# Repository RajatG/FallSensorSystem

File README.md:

# Fall Sensor System (IoT Firmware, KiCad PCB Hardware & Android Mobile App)

An ultra-low-power, dual-radar fall detection and room occupancy monitoring system engineered for ceiling and wall mounting with battery autonomy.

---

## 📁 Repository Overview

```
├── firmware/                        # Microcontroller & Radar Firmware
│   ├── fall_sensor_esp32_C1001_v1/  # ESP32 Firmware for C1001 60GHz Radar (v4.23)
│   ├── fall_sensor_esp32_ld2410_v1/ # ESP32 Firmware for LD2410 24GHz Radar (v4.23)
│   ├── fall_attiny_v1/              # ATtiny85 Low-Power Wake Sentinel (v4.8)
│   └── fall_attiny_mic_debug/       # ATtiny85 MIC Hardware Debug Utility
│
├── hardware/                        # KiCad 10.0 PCB & Schematic Files
│   ├── fall_sensor.kicad_sch        # Main System Schematic
│   ├── fall_sensor.kicad_pcb        # 2-Layer PCB Layout
│   ├── fall_sensor.kicad_pro        # KiCad Project Configuration
│   ├── FallSensor.kicad_sym     # Custom Symbol Library
│   ├── FallSensor.pretty/       # Custom Footprint Library
│   └── export/
│       ├── fall_sensor_gerbers.zip  # Production Gerber & Drill Package (JLCPCB/PCBWay)
│       └── pdf/                     # Printable Documentation (See hardware/export/pdf/README.md)
│           ├── fall_sensor_pcb_front_and_back_A4.pdf  # 1:1 True Scale Paper Testing Sheet
│           ├── fall_sensor_schematic_A4_printable.pdf # Printable A4 Schematic
│           ├── assembly/            # Top & Bottom Assembly Drawings
│           ├── layers/              # Top & Bottom Copper Layer Plots
│           └── schematic/           # Full-Size A3 Engineering Schematic
│
├── enclosure/                       # 3D Printed Wall-Mount Enclosure (v2.1 Square)
│   ├── fall_sensor_enclosure_base.stl # Base Mount with 18650 Battery Bay & PCB Standoffs
│   ├── fall_sensor_enclosure_lid.stl  # Front Cover with Apertures & Alignment Lip
│   ├── build_square_enclosure.py      # Parametric Blender Python CAD Script (v2.1)
│   ├── fall_sensor_enclosure.blend    # Master Blender CAD Project & Studio Renders
│   └── README.md                      # Mechanical Specifications & Slicer Guide
│
├── mobile_app/                      # Android Companion App (Jetpack Compose)
│   ├── app/                         # Source Code supporting C1001 & LD2410 Flavors
│   ├── build.gradle.kts
│   └── ...
│
└── docs/                            # Architectural Specs, Roadmaps & Engineering Docs (See docs/README.md)
    ├── README.md                    # Master Documentation Hub & Flow Map
    ├── Firmware_Architecture_and_Detection_Logic.md  # Complete Firmware Logic & 4-Layer Fall Pipeline
    ├── Master_4Stream_Roadmap_and_Recommendations.md # Comprehensive 4-Stream Status & Production Roadmap
    ├── PCB_Component_Connections_Verification.md     # Master 21-Component Netlist & Pinout Verification Guide
    ├── PCB_Component_Footprints_and_Dimensions.md    # Physical Dimensions, Drills & Pad Pitch Reference
    ├── SMD_BOM_Master_List.md       # Production SMD Component Master List (Rev B)
    ├── SMD_Hardware_Architecture.md # Power-path, Charger & Protection Circuitry Specs
    ├── C1001_Early_Exit_Analysis.md # Radar Optimization & Timing Breakdown
    └── ATtiny85_MIC_Analysis.md     # Sentinel Threshold & Acoustic Filter Specs
```

---

## ⚡ System Overview & Architecture

### What the System Is
The **Fall Sensor System** is a privacy-first, contactless room occupancy and fall detection device designed for elder care and clinical environments. It eliminates the need for cameras, audio-recording microphones, or wearable pendants.

### How it Works: The Staged-Wakeup Architecture
Operating mmWave radar continuously requires 60–120 mA, which would exhaust a battery in under two days. To achieve long battery life on a single 18650 cell, the system uses an **asymmetric staged-wakeup architecture**:

```
+-----------------------------------------------------------------------------------+
| 1. PASSIVE SENSING (Continuous ~35uA Draw)                                        |
|    - AM312 PIR watches for motion cone entry.                                     |
|    - LM393 acoustic sensor watches for mechanical floor impact shockwaves.       |
|    - ATtiny85 Sentinel debounces signals while ESP32 and Radar sleep.             |
+-----------------------------------------+-----------------------------------------+
                                          | Valid Motion or Thud Pulse
                                          v
+-----------------------------------------------------------------------------------+
| 2. RADAR VERIFICATION SNAPSHOT (2.5s - 4.0s Window)                               |
|    - ESP32 wakes from deep sleep and gates Radar power via MOSFET switch.         |
|    - mmWave Radar measures distance, target velocity, and floor-level coordinates.|
+-----------------------------------------+-----------------------------------------+
                                          |
                      +-------------------+-------------------+
                      |                                       |
              [ Normal Upright Motion ]               [ Confirmed Fall ]
                      |                                       |
                      v                                       v
+---------------------------------------------+ +-----------------------------------+
| 3. SMART EARLY EXIT                         | | 4. IMMEDIATE ALERTING             |
|    - Target confirmed standing/walking.     | |    - Red Fall Siren LED activates.|
|    - Radar cuts power at 2.5s - 4.0s.       | |    - BLE alert packet transmitted |
|    - BLE occupancy status updated.          | |      to Android caregiver app.    |
|    - ESP32 returns to deep sleep (<15uA).   | |    - Persists until recovery or   |
|      (Saves ~90% energy per event)          | |      manual sync button reset.    |
+---------------------------------------------+ +-----------------------------------+
```

---

## 📦 Engineering Streams & Subunit Documentation

The system is organized into four self-contained, documented engineering streams:

| Stream | Subunit Directory | Key Deliverables & Documentation |
|---|---|---|
| **⚡ Firmware** | [`firmware/`](firmware/README.md) | ESP32 C1001 & LD2410 drivers, ATtiny85 wake sentinel, v4.23 Gradual Posture Collapse detection, and flashing guides. |
| **🔌 Hardware (PCB)** | [`hardware/`](hardware/README.md) | KiCad 10.0 schematics, 2-layer PCB ($100 \times 80\text{ mm}$), pin mapping table, Gerbers, and 1:1 scale printable test sheets. |
| **🖨️ 3D Enclosure** | [`enclosure/`](enclosure/README.md) | v2.1 Square CAD model ($116.8 \times 110.8 \times 31.4\text{ mm}$), 18650 battery cradle, STL meshes, slicer settings, and photorealistic renders. |
| **📱 Mobile App** | [`mobile_app/`](mobile_app/README.md) | Android companion application (Jetpack Compose, Kotlin, BLE GATT), telemetry parser, and build flavor instructions. |
| **📚 Documentation** | [`docs/`](docs/README.md) | Master documentation hub, 4-layer fall logic specification, radar early exit analysis, acoustic sensitivity analysis, and SMD Rev B migration roadmap. |

---

## 🚀 Quick Manufacturing & Test Links

* **PCB Fabrication Gerbers:** [`hardware/export/fall_sensor_gerbers.zip`](hardware/export/fall_sensor_gerbers.zip) (Ready for JLCPCB/PCBWay upload).
* **1:1 Scale Paper Test Sheet:** [`hardware/export/pdf/fall_sensor_pcb_front_and_back_A4.pdf`](hardware/export/pdf/fall_sensor_pcb_front_and_back_A4.pdf) (For physical component fitting).
* **3D Printable STLs:** [`enclosure/fall_sensor_enclosure_base.stl`](enclosure/fall_sensor_enclosure_base.stl) and [`enclosure/fall_sensor_enclosure_lid.stl`](enclosure/fall_sensor_enclosure_lid.stl).
* **1:1 Scale 3D PCB Test Plate:** [`enclosure/fall_sensor_pcb_dummy.stl`](enclosure/fall_sensor_pcb_dummy.stl) (True KiCad 3D mesh with all 186 through-hole drill cutouts for physical pin-alignment and base cavity test-fitting).

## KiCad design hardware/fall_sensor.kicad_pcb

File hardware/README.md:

# 🔌 Hardware CAD & PCB Engineering (KiCad 10.0)

This directory contains the complete electronic schematic and PCB design files for the Fall Sensor System prototype (Rev A).

---

## 📁 Hardware Files

| File / Folder | Type | Description |
|---|:---:|---|
| **[`fall_sensor.kicad_sch`](fall_sensor.kicad_sch)** | Schematic | Main system schematic in KiCad 10 format. |
| **[`fall_sensor.kicad_pcb`](fall_sensor.kicad_pcb)** | PCB Layout | 2-layer, $100.00 \times 80.00\text{ mm}$ printed circuit board layout. |
| **[`fall_sensor.kicad_pro`](fall_sensor.kicad_pro)** | Project Config | KiCad project workspace and design rules. |
| **[`FallSensor.kicad_sym`](FallSensor.kicad_sym)** | Symbol Library | Custom schematic symbols for breakout modules. |
| **[`FallSensor.pretty/`](FallSensor.pretty/)** | Footprint Library | Custom PCB footprints for daughterboards and sensors. |
| **[`export/`](export/)** | Production Files | Manufacturing Gerbers and printable PDF packages. |

---

## 📐 PCB Specifications

* **Board Dimensions:** $100.00\text{ mm} \times 80.00\text{ mm}$
* **Layer Count:** 2-Layer FR4 ($1.6\text{ mm}$ thickness, $1\text{ oz}$ / $35\mu\text{m}$ copper)
* **Design Rule Status:** **0 DRC Errors, 0 Unconnected Nets**
* **Power Architecture:** Dual switched rails (Protected Li-Ion Battery $\rightarrow$ 5.0V Boost $\rightarrow$ 3.3V Step-Down).
* **Radar Gating:** High-side/low-side N-Channel MOSFET load switch controlled via GPIO 27.

---

## 📌 Microcontroller Pinout & Net Mapping

### ESP32 DevKit V1 (30-Pin) Net Connections
| Pin # | Label | Connected Net | Hardware Destination & Role |
|:---:|---|---|---|
| **1** | `3V3` | `+3V3` | Regulated 3.3V power input from U7 buck converter |
| **5** | `GPIO34` | `/BATT_ADC` | Midpoint of 100kΩ/100kΩ battery sensing divider |
| **8** | `GPIO33` | `Net-(U1-GPIO33)` | Tactile Sync & Alarm Clear Button (`SW1`) |
| **9** | `GPIO25` | `/PRESENCE` | C1001 radar hardware presence flag (`OUT1`) |
| **10** | `GPIO26` | `/FALL` | C1001 radar hardware fall detection flag (`OUT2`) |
| **11** | `GPIO27` | `/RADAR_EN` | Load switch gate control (energizes radar power rail) |
| **14** | `GND` | `GND` | Common system ground plane |
| **15** | `GPIO13` | `/PIR_WAKE` | Motion wake interrupt from ATtiny85 Sentinel (`PB2`) |
| **19** | `GPIO19` | `Net-(U1-GPIO19)` | Status Fall Alarm LED (`D1`) via 270Ω resistor |
| **26** | `GPIO17` | `/RADAR_RX` | Hardware UART RX $\leftarrow$ C1001 radar TX |
| **27** | `GPIO16` | `/RADAR_TX` | Hardware UART TX $\rightarrow$ C1001 radar RX |
| **28** | `GPIO4` | `/MIC_WAKE` | Acoustic impact wake interrupt from ATtiny85 Sentinel (`PB0`) |

### ATtiny85 Sentinel Pin Mapping
| Pin # | Label | Connected Net | Hardware Destination & Role |
|:---:|---|---|---|
| **2** | `PB4` | `Net-(U2-P4)` | Digital acoustic trigger input from LM393 (`DO`) |
| **5** | `PB1` | `Net-(PIR1-OUT)` | Digital motion trigger input from AM312 PIR (`OUT`) |
| **6** | `PB0` | `/MIC_WAKE` | Active-HIGH 50ms wake pulse to ESP32 `GPIO4` |
| **4** | `PB2` | `/PIR_WAKE` | Active-HIGH 50ms wake pulse to ESP32 `GPIO13` |
| **7** | `GND` | `GND` | Common ground |
| **8** | `VIN` | *Unconnected* | Bypassed (Digispark onboard regulator not used) |
| **9** | `5V/VCC` | `+3V3` | Regulated 3.3V power input from U7 buck converter |

---

## 📦 Manufacturing & Test Deliverables

* **Gerber Package:** [`export/fall_sensor_gerbers.zip`](export/fall_sensor_gerbers.zip) — Ready for direct upload to JLCPCB, PCBWay, or OSH Park.
* **1:1 True Scale Paper Testing Sheet:** [`export/pdf/fall_sensor_pcb_front_and_back_A4.pdf`](export/pdf/fall_sensor_pcb_front_and_back_A4.pdf) — Verified 1:1 A4 sheet with 10.0 cm calibration ruler for physical component fit-testing.
* **Assembly & Layer Drawings:** See [`export/pdf/README.md`](export/pdf/README.md) for top/bottom silkscreen and layer plots.

---

## 📖 Detailed Engineering References
* Complete 21-component netlist and verification tables: [`../docs/PCB_Component_Connections_Verification.md`](../docs/PCB_Component_Connections_Verification.md)
* Physical package outlines, drill sizes, and pad-to-pad pitches: [`../docs/PCB_Component_Footprints_and_Dimensions.md`](../docs/PCB_Component_Footprints_and_Dimensions.md)
* Production SMD Component Master List (Rev B): [`../docs/SMD_BOM_Master_List.md`](../docs/SMD_BOM_Master_List.md)

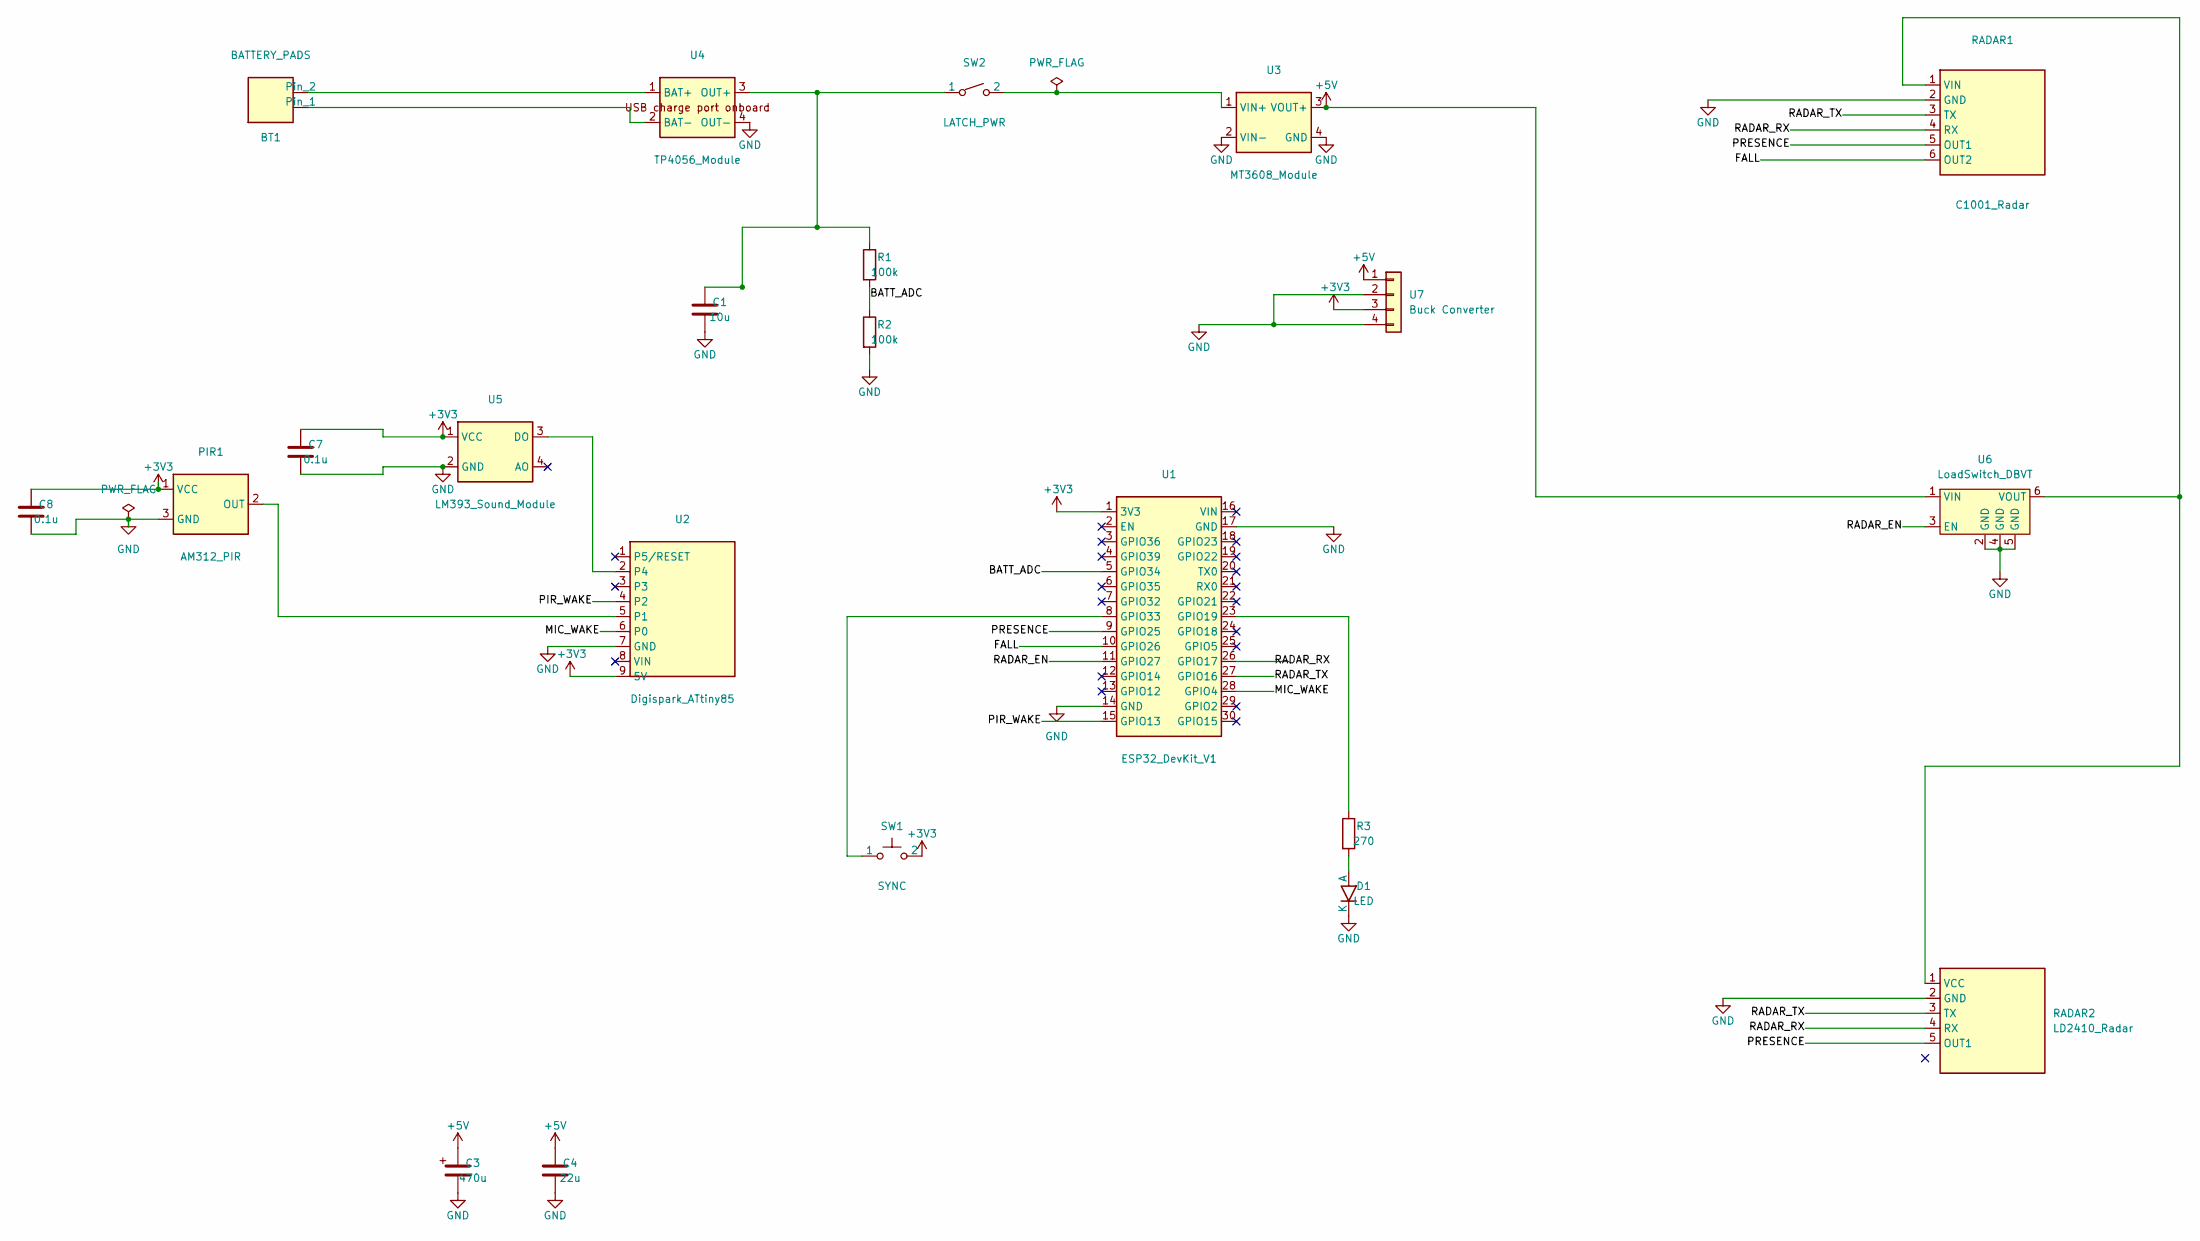
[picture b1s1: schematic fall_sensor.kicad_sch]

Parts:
BT1: BATTERY_PADS; PinHeader_1x02_P2.54mm_Vertical
C1: 10u; C_Disc_D5.0mm_W2.5mm_P5.00mm
C3: 470u; CP_Radial_D8.0mm_P3.50mm
C4: 22u; C_Disc_D5.0mm_W2.5mm_P5.00mm
C7, C8: 0.1u; C_Disc_D5.0mm_W2.5mm_P5.00mm
D1: LED; LED_D3.0mm
PIR1: AM312_PIR; AM312_PIR_Square22x20
R1, R2: 100k; R_Axial_DIN0207_L6.3mm_D2.5mm_P10.16mm_Horizontal
R3: 270; R_Axial_DIN0207_L6.3mm_D2.5mm_P10.16mm_Horizontal
RADAR1: C1001_Radar; C1001_Module
RADAR2: LD2410_Radar; LD2410_1.27mm
SW1: SYNC; SW_PUSH_6mm
SW2: LATCH_PWR; PinHeader_1x02_P2.54mm_Vertical
U1: ESP32_DevKit_V1; ESP32_DevKit_DOIT_2x15
U2: Digispark_ATtiny85; Digispark_9Pin_RightAngle
U3: MT3608_Module
U4: TP4056_Module
U5: LM393_Sound_Module
U6: LoadSwitch_DBVT; DIP-6_W7.62mm
U7: Buck Converter; LM2596_Module

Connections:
+3V3: C7.1, C8.1, PIR1.1 (VCC), SW1.2, U1.1 (3V3), U2.9 (5V), U5.1 (VCC), U7.3
+5V: C3.1, C4.1, U3.3 (VOUT+), U6.1 (VIN), U7.1
/BATT_ADC: R1.2, R2.1, U1.5 (GPIO34)
/FALL: RADAR1.6 (OUT2), U1.10 (GPIO26)
/MIC_WAKE: U1.28 (GPIO4), U2.6 (P0)
/PIR_WAKE: U1.15 (GPIO13), U2.4 (P2)
/PRESENCE: RADAR1.5 (OUT1), RADAR2.5 (OUT1), U1.9 (GPIO25)
/RADAR_EN: U1.11 (GPIO27), U6.3 (EN)
/RADAR_RX: RADAR1.4 (RX), RADAR2.4 (RX), U1.26 (GPIO17)
/RADAR_TX: RADAR1.3 (TX), RADAR2.3 (TX), U1.27 (GPIO16)
GND: C1.2, C3.2, C4.2, C7.2, C8.2, D1.2 (K), PIR1.3 (GND), R2.2, RADAR1.2 (GND), RADAR2.2 (GND), U1.14 (GND), U1.17 (GND), U2.7 (GND), U3.2 (VIN-), U3.4 (GND), U4.4 (OUT-), U5.2 (GND), U6.2 (GND), U6.4 (GND), U6.5 (GND), U7.2, U7.4
unnamed: BT1.1, U4.2 (BAT-)
unnamed: BT1.2, U4.1 (BAT+)
unnamed: D1.1 (A), R3.2
unnamed: PIR1.2 (OUT), U2.5 (P1)
unnamed: RADAR1.1 (VIN), RADAR2.1 (VCC), U6.6 (VOUT)
unnamed: R3.1, U1.23 (GPIO19)
unnamed: SW1.1, U1.8 (GPIO33)
unnamed: U2.2 (P4), U5.3 (DO)
unnamed: SW2.2, U3.1 (VIN+)
unnamed: C1.1, R1.1, SW2.1, U4.3 (OUT+)

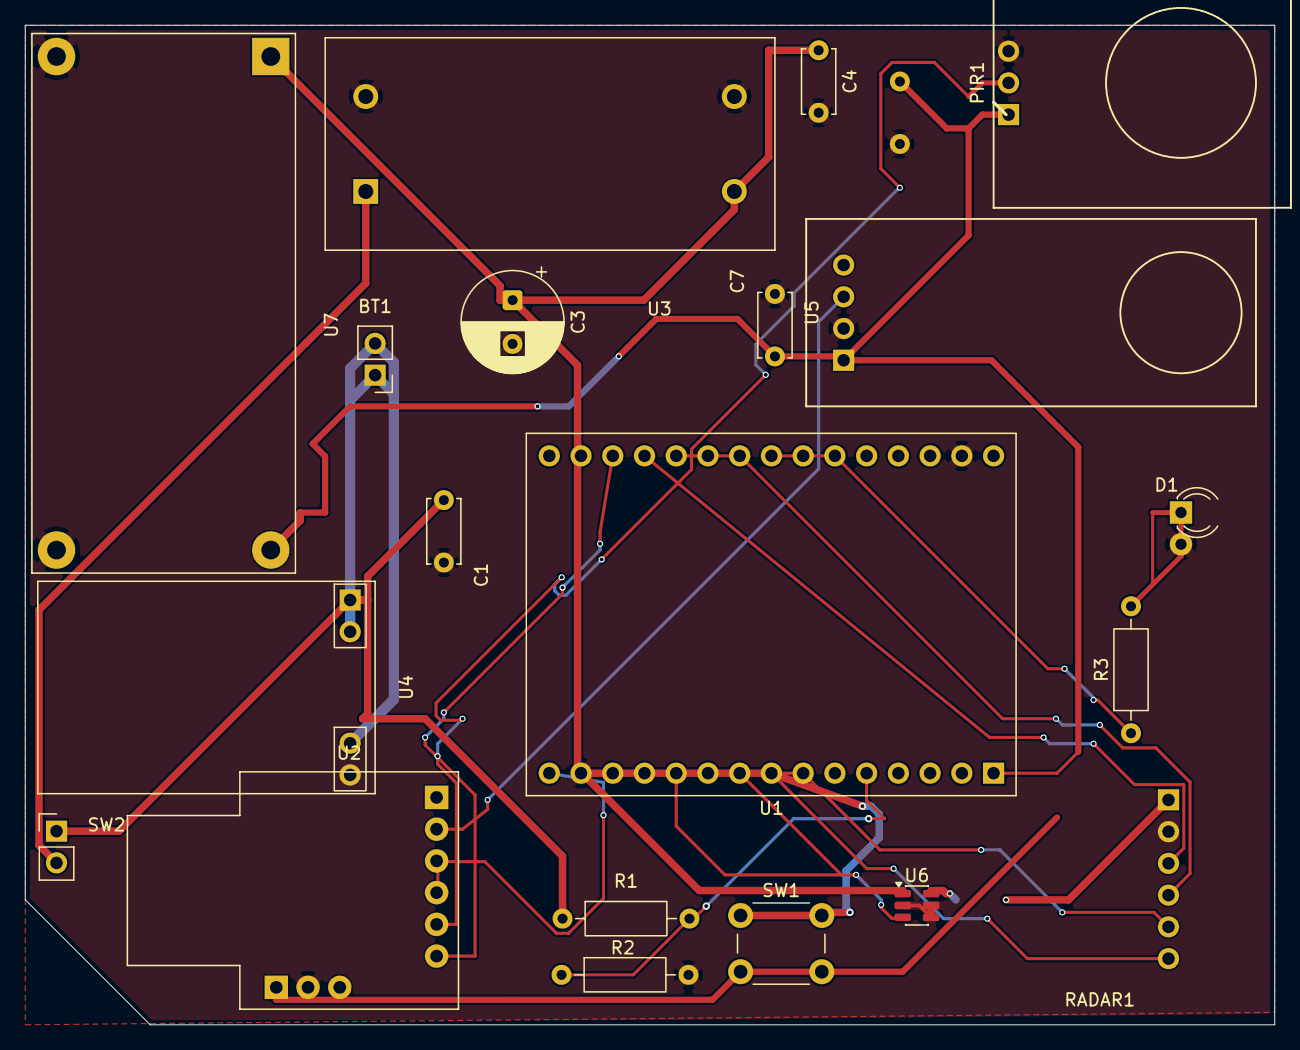
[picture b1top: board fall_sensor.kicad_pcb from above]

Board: 2 copper layers, 100.0 x 80.0 mm, 21 parts (1 on the bottom side), 21 nets.

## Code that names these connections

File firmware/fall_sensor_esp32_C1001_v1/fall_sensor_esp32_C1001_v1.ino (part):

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RTC_DATA_ATTR int roomHeightCm = 274;         
RTC_DATA_ATTR int floorToleranceCm = 45;      // Target detected between (roomHeight - 45) and (roomHeight + 35) is at floor level
RTC_DATA_ATTR int floorLyingConsecutiveChecks = 0; // Number of consecutive periodic checks target remains on floor
const int FLOOR_LYING_ALERT_THRESHOLD = 2;   // 2 consecutive checks (~60-120s) triggers static fall alarm
RTC_DATA_ATTR int lastStandingDistCm = 0;          // Last distance when person was in standing zone
RTC_DATA_ATTR unsigned long lastStandingTime = 0;   // millis() when last seen standing

// --- HARDWARE PINS ---
#define PIR_WAKE_PIN     13  
#define MIC_WAKE_PIN     4   
#define PRESENCE_PIN     25  // C1001 OUT1
#define FALL_PIN         26  // C1001 OUT2
#define SYNC_BUTTON_PIN  33  
#define BATTERY_PIN      34  
#define RADAR_MOSFET_PIN 27  
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  
  if (infinite) {
      // Infinite sleep: wake on PIR, MIC, or SYNC button
      uint64_t bitmask = (1ULL << PIR_WAKE_PIN) | (1ULL << MIC_WAKE_PIN) | (1ULL << SYNC_BUTTON_PIN);
      esp_sleep_enable_ext1_wakeup(bitmask, ESP_EXT1_WAKEUP_ANY_HIGH);
  } else {
      // Periodic 60s sleep: Allow Acoustic Impact THUD (MIC) and SYNC button to interrupt immediately!
      // (PIR walking motion is ignored to prevent battery drain in occupied room)
      uint64_t bitmask = (1ULL << SYNC_BUTTON_PIN) | (1ULL << MIC_WAKE_PIN);
      esp_sleep_enable_ext1_wakeup(bitmask, ESP_EXT1_WAKEUP_ANY_HIGH);
      esp_sleep_enable_timer_wakeup(PERIODIC_SLEEP_SEC * 1000000ULL);
  }
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void setup() {
  pinMode(RADAR_MOSFET_PIN, OUTPUT);
  pinMode(FALL_LED_PIN, OUTPUT);
  pinMode(PRESENCE_PIN, INPUT_PULLUP);
  pinMode(FALL_PIN, INPUT_PULLUP);
  pinMode(SYNC_BUTTON_PIN, INPUT_PULLDOWN);
  pinMode(PIR_WAKE_PIN, INPUT_PULLDOWN);
  pinMode(MIC_WAKE_PIN, INPUT_PULLDOWN);
  
  rtc_gpio_pulldown_en((gpio_num_t)PIR_WAKE_PIN);
  rtc_gpio_pulldown_en((gpio_num_t)MIC_WAKE_PIN);
  rtc_gpio_pullup_dis((gpio_num_t)MIC_WAKE_PIN);
  rtc_gpio_pulldown_en((gpio_num_t)SYNC_BUTTON_PIN);

  attachInterrupt(digitalPinToInterrupt(SYNC_BUTTON_PIN), syncButtonISR, RISING);
  attachInterrupt(digitalPinToInterrupt(PIR_WAKE_PIN), pirISR, RISING);
  attachInterrupt(digitalPinToInterrupt(MIC_WAKE_PIN), micISR, RISING);

  digitalWrite(RADAR_MOSFET_PIN, LOW);
  digitalWrite(FALL_LED_PIN, LOW);
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  esp_sleep_wakeup_cause_t wakeup_reason = esp_sleep_get_wakeup_cause();
  if (wakeup_reason == ESP_SLEEP_WAKEUP_EXT1) {
    uint64_t wakeup_pin_mask = esp_sleep_get_ext1_wakeup_status();
    if (wakeup_pin_mask & (1ULL << PIR_WAKE_PIN)) {
      currentTrigger = PIR_WALK_IN;
      lastPirLogTime = 0; // Force immediate log
    } else if (wakeup_pin_mask & (1ULL << MIC_WAKE_PIN)) {
      currentTrigger = MIC_THUD;
      lastMicLogTime = 0; // Force immediate log
    } else if (wakeup_pin_mask & (1ULL << SYNC_BUTTON_PIN)) {
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  // --- C1001 Radar Logic (Pins + UART Fallback) ---
  if (isRadarPowered) {
      
      int rawPin25 = digitalRead(PRESENCE_PIN);
      int rawPin26 = digitalRead(FALL_PIN);
      
      bool uartPresence = (hu.dmHumanData(hu.eExistence) == 1);
      int fallState = hu.getFallData(hu.eFallState);  // Cache result — calling twice corrupts UART buffer!
      bool uartFall = (fallState == 1 || fallState == 2);
      
      // Hardware Pin presence: GPIO fast-path for early exit (same pattern as LD2410)
      bool hardwarePresence = (rawPin25 == HIGH);
      bool hardwareFall = (rawPin26 == HIGH);
      
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          bool valuesChanged = (rawPin25 != lastLoggedHWPres) || (uartPresence != lastLoggedUARTPres) || (rawPin26 != lastLoggedHWFall) || (uartFall != lastLoggedUARTFall) || (dist != lastLoggedDist);
          bool heartbeatDue = (millis() - lastHeartbeatLog > HEARTBEAT_LOG_INTERVAL);
          if (valuesChanged || heartbeatDue) {
              String logMsg = "[RADAR] Pin25_RAW: " + String(rawPin25) + " | Pin26_RAW: " + String(rawPin26) + " | UART Pres: " + String(uartPresence) + " | UART Fall: " + String(uartFall) + " | Dist: " + String(dist) + "cm";
              if (isAtFloorLevel) logMsg += " [FLOOR LEVEL]";
              logMsg += "\n";
              sendBLENotification(logMsg.c_str());
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          if (currentTrigger == BOOT) checkLabel = "Startup";
          else if (currentTrigger == PERIODIC_TIMER) checkLabel = "Periodic";
          else if (currentTrigger == PIR_WALK_IN) checkLabel = "PIR Walk-In";
          else if (currentTrigger == MIC_THUD) checkLabel = "MIC Thud Fall Evaluation";
          
          if (presenceDetected) {
              if (!wasOccupied) {
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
